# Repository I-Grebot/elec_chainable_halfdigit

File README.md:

# Chainable half-digit

## Requirements

Files inside `3d_models` folder must be copied into `<kicad dir>\share\kicad\modules\packages3d`

## Resources

WS2812B library downloaded from https://github.com/madworm/WS2812B.pretty

WS2812B 3d model downloaded from https://github.com/KiCad/kicad-library/pull/889/commits/e64ddbc4951541991125f50d6662f56ea14219c8

Arduino Nano library downloaded from http://sylvain.fish.free.fr/kicad_lib/

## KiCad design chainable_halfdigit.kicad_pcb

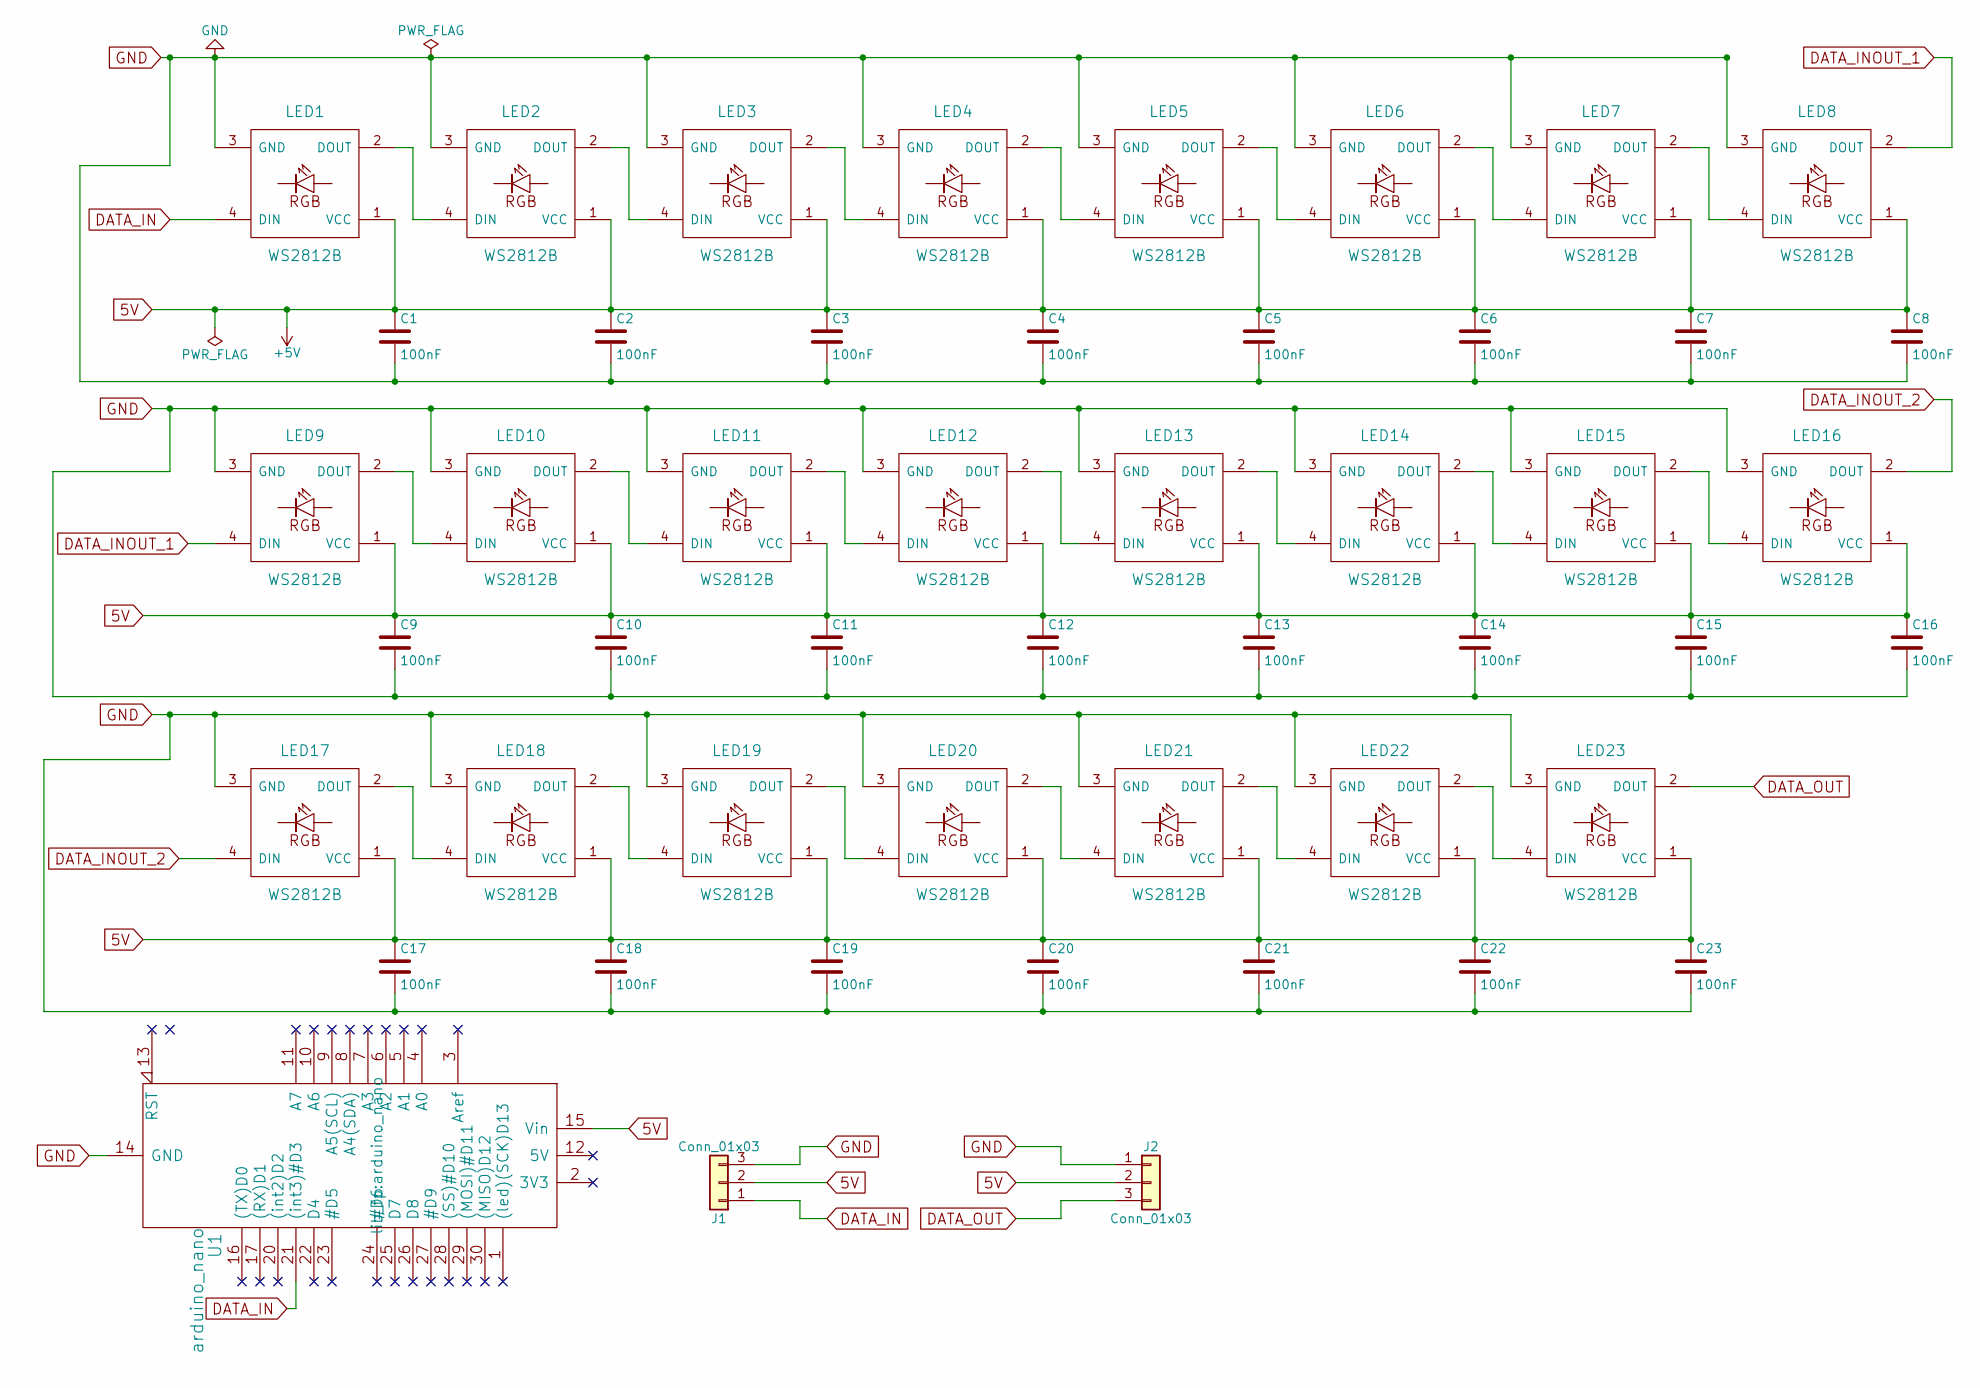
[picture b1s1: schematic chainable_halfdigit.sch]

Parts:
C1, C2, C3, C4, C5, C6, C7, C8, C9, C10, C11, C12, C13, C14, C15, C16, C17, C18, C19, C20, C21, C22, C23: 100nF; C_0603
J1, J2: Conn_01x03; Pin_Header_Straight_1x03_Pitch2.54mm
LED1, LED2, LED3, LED4, LED5, LED6, LED7, LED8, LED9, LED10, LED11, LED12, LED13, LED14, LED15, LED16, LED17, LED18, LED19, LED20, LED21, LED22, LED23: WS2812B; WS2812B_data-bridgeable
U1: arduino_nano

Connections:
5V: C1.1, C2.1, C3.1, C4.1, C5.1, C6.1, C7.1, C8.1, C9.1, C10.1, C11.1, C12.1, C13.1, C14.1, C15.1, C16.1, C17.1, C18.1, C19.1, C20.1, C21.1, C22.1, C23.1, J1.2, J2.2, LED1.1 (VCC), LED2.1 (VCC), LED3.1 (VCC), LED4.1 (VCC), LED5.1 (VCC), LED6.1 (VCC), LED7.1 (VCC), LED8.1 (VCC), LED9.1 (VCC), LED10.1 (VCC), LED11.1 (VCC), LED12.1 (VCC), LED13.1 (VCC), LED14.1 (VCC), LED15.1 (VCC), LED16.1 (VCC), LED17.1 (VCC), LED18.1 (VCC), LED19.1 (VCC), LED20.1 (VCC), LED21.1 (VCC), LED22.1 (VCC), LED23.1 (VCC), U1.15 (Vin)
DATA_IN: J1.1, LED1.4 (DIN), U1.21 ((int3)#D3)
DATA_INOUT_1: LED8.2 (DOUT), LED9.4 (DIN)
DATA_INOUT_2: LED16.2 (DOUT), LED17.4 (DIN)
DATA_OUT: J2.3, LED23.2 (DOUT)
GND: C1.2, C2.2, C3.2, C4.2, C5.2, C6.2, C7.2, C8.2, C9.2, C10.2, C11.2, C12.2, C13.2, C14.2, C15.2, C16.2, C17.2, C18.2, C19.2, C20.2, C21.2, C22.2, C23.2, J1.3, J2.1, LED1.3 (GND), LED2.3 (GND), LED3.3 (GND), LED4.3 (GND), LED5.3 (GND), LED6.3 (GND), LED7.3 (GND), LED8.3 (GND), LED9.3 (GND), LED10.3 (GND), LED11.3 (GND), LED12.3 (GND), LED13.3 (GND), LED14.3 (GND), LED15.3 (GND), LED16.3 (GND), LED17.3 (GND), LED18.3 (GND), LED19.3 (GND), LED20.3 (GND), LED21.3 (GND), LED22.3 (GND), LED23.3 (GND), U1.14 (GND), U1.19 (GND)
unnamed: LED1.2 (DOUT), LED2.4 (DIN)
unnamed: LED2.2 (DOUT), LED3.4 (DIN)
unnamed: LED3.2 (DOUT), LED4.4 (DIN)
unnamed: LED4.2 (DOUT), LED5.4 (DIN)
unnamed: LED5.2 (DOUT), LED6.4 (DIN)
unnamed: LED6.2 (DOUT), LED7.4 (DIN)
unnamed: LED7.2 (DOUT), LED8.4 (DIN)
unnamed: LED10.2 (DOUT), LED11.4 (DIN)
unnamed: LED9.2 (DOUT), LED10.4 (DIN)
unnamed: LED11.2 (DOUT), LED12.4 (DIN)
unnamed: LED12.2 (DOUT), LED13.4 (DIN)
unnamed: LED13.2 (DOUT), LED14.4 (DIN)
unnamed: LED14.2 (DOUT), LED15.4 (DIN)
unnamed: LED15.2 (DOUT), LED16.4 (DIN)
unnamed: LED17.2 (DOUT), LED18.4 (DIN)
unnamed: LED18.2 (DOUT), LED19.4 (DIN)
unnamed: LED19.2 (DOUT), LED20.4 (DIN)
unnamed: LED20.2 (DOUT), LED21.4 (DIN)
unnamed: LED21.2 (DOUT), LED22.4 (DIN)
unnamed: LED22.2 (DOUT), LED23.4 (DIN)

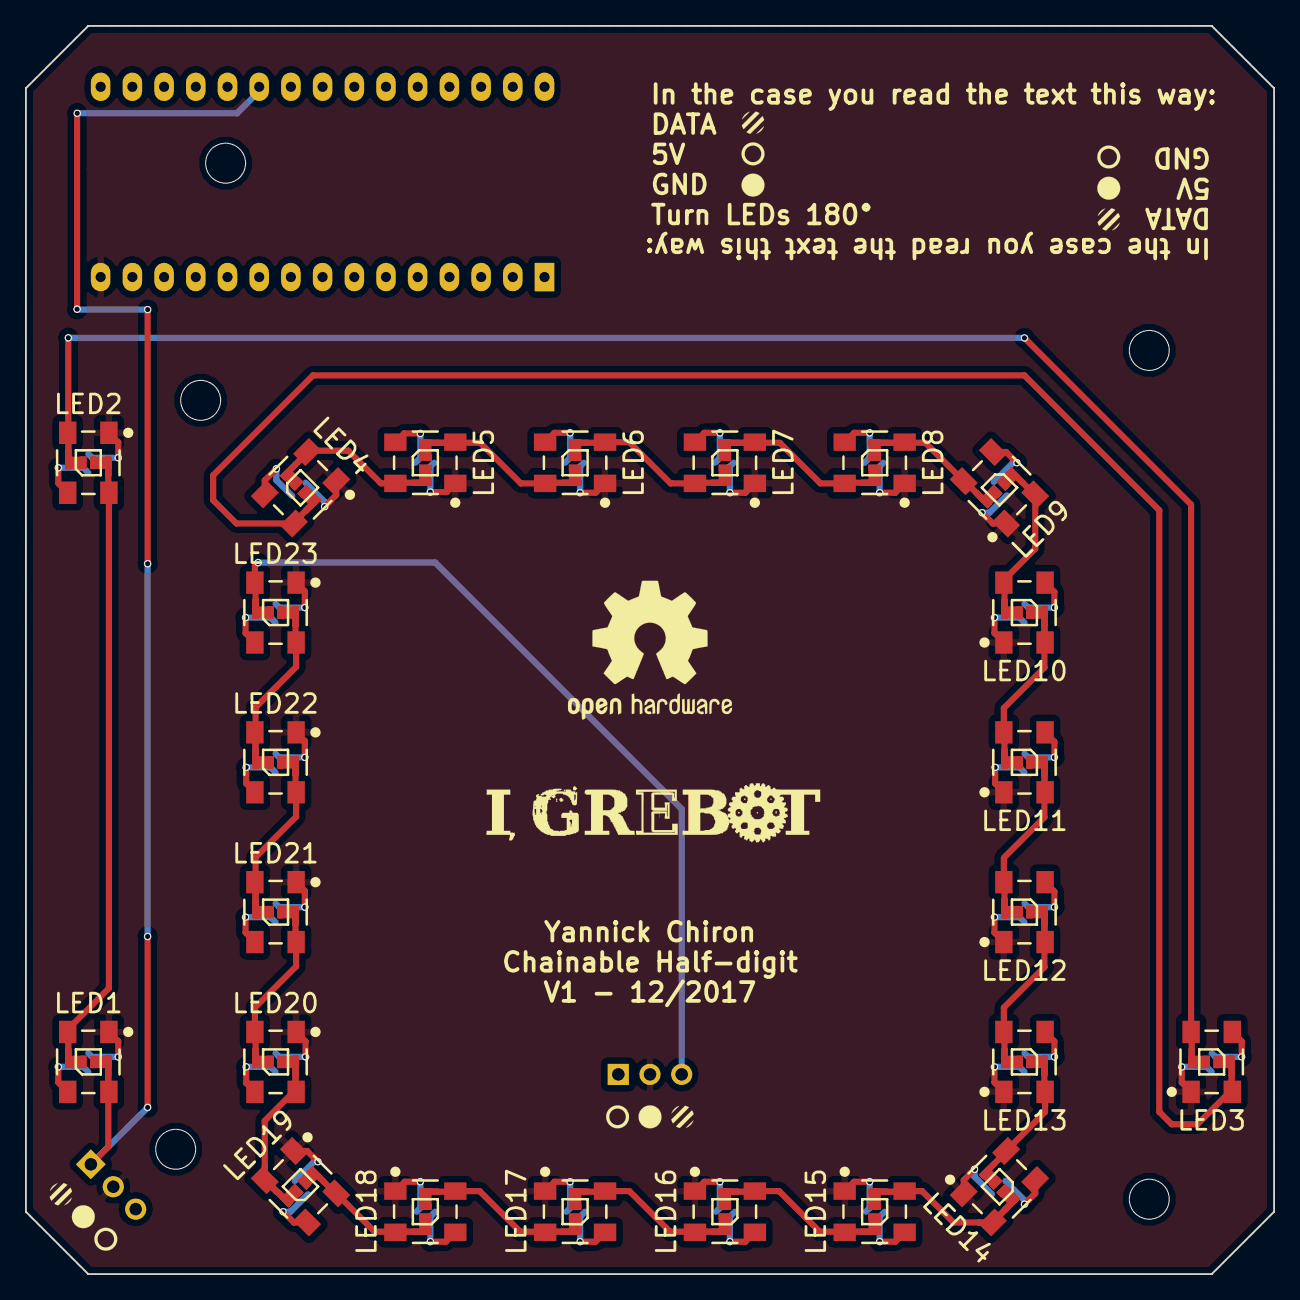
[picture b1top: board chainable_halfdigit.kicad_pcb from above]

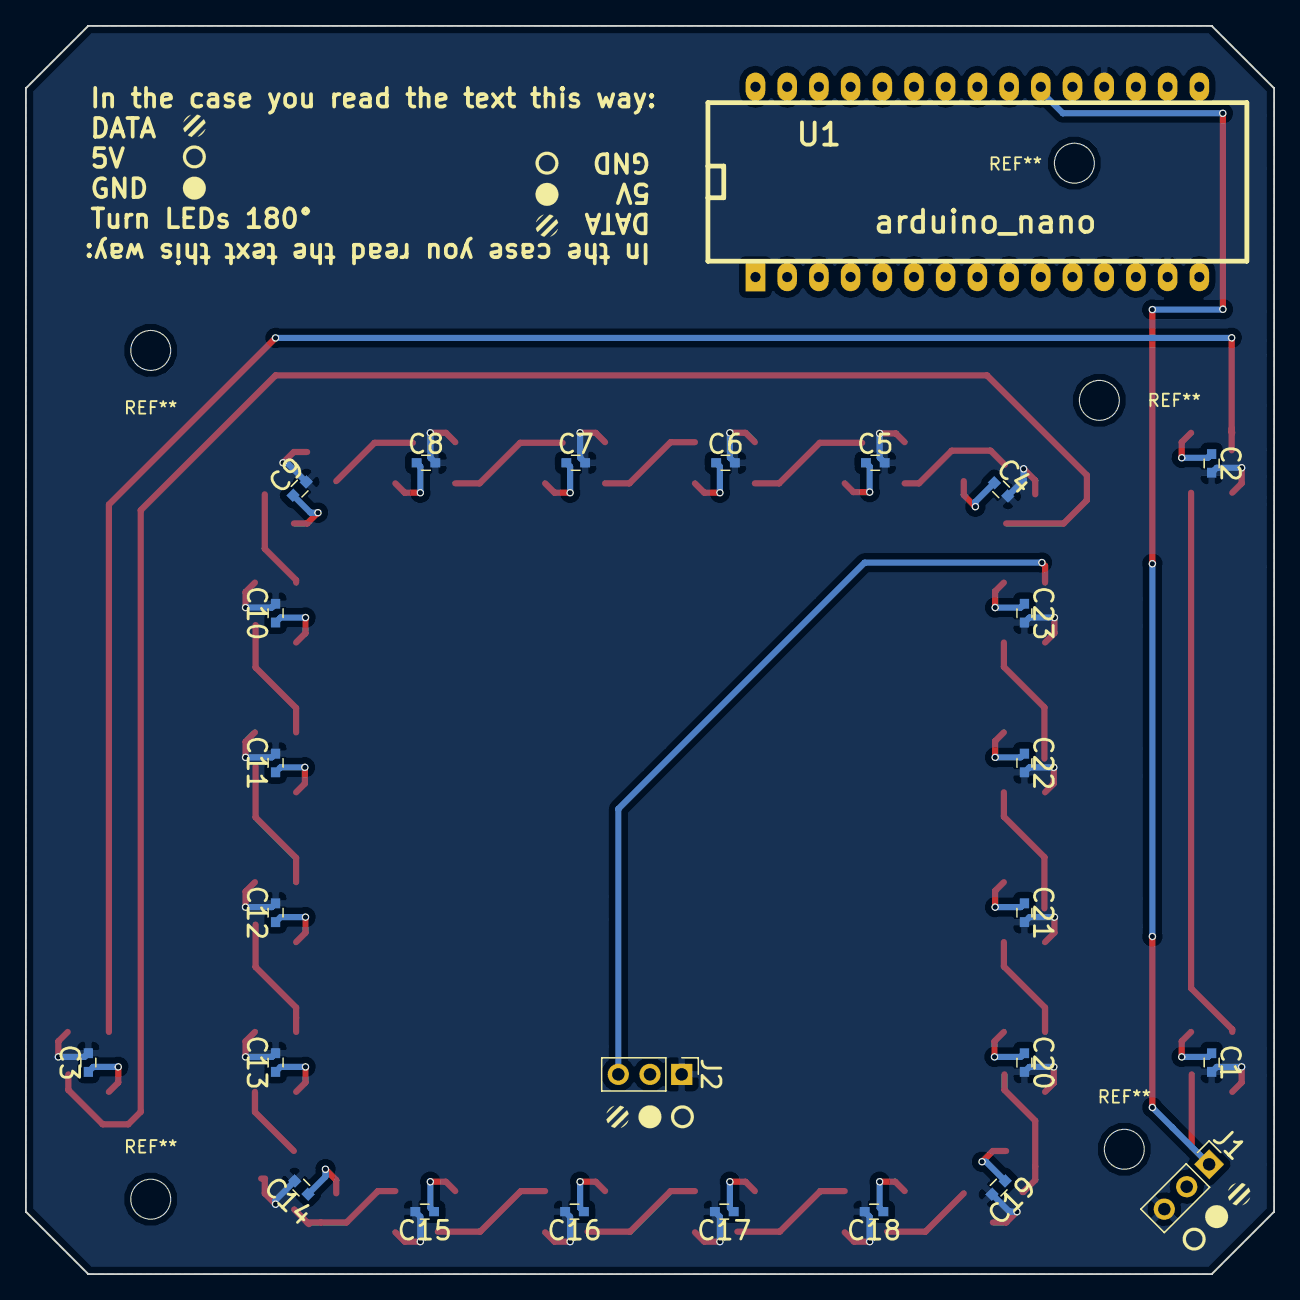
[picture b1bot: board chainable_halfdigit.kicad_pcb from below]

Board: 2 copper layers, 100.0 x 100.0 mm, 49 parts (26 on the bottom side), 26 nets.

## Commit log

2017-11-07 Added schematic
2017-11-07 Added more LEDs and created PCB
2017-11-07 Exported schematic image
2017-11-08 Updated readme image link
2017-11-09 Placed components in PCB
2017-11-09 Made pretty lib as local. Added 3D model to leds.
2017-11-09 Added tracks
2017-11-09 Edited net sizes
2017-11-10 Added optionnal capacitors between 5v and gnd to make the pcb reversable
2017-11-10 Revert "Added optionnal capacitors between 5v and gnd to make the pcb reversable"
    This reverts commit ca0c5a413a5eb6350914f70d9c814ea12825b423.
2017-11-10 Added instructions on PCB
2017-11-11 Reverse 5V and DATA to avoid circuit damage when reversing connector.
2017-11-12 Moved connectors and capacitors on back layer
2017-11-12 Increase 'value' labels sizes
2017-11-26 Added Arduino Nano footprint
2017-11-26 Removed unnecessary nRF24L01 library
2017-11-26 Edited arduino nano 3D model
2017-11-27 Fixed README.md formating and removed reference to NRF24L01+ resource
2017-11-27 Placed mounting holes, updated WS2812B footprint with PIN1 marker.
2017-11-27 updated plot with latest changes
2017-11-28 Changed DATA_IN in arduino nano from D4 to D3. Moved some components.
2017-11-30 Added a mounting hole, edited some tracks
2017-11-30 Added info and logo
2017-12-02 Exported gerber
2017-12-04 Fixed 5V/GND legend (was inverted)
2017-12-17 Totated instructions 180°, so controller can be placed bottom right.
2017-12-17 Missing file from last commit
2017-12-17 Fixed legend
